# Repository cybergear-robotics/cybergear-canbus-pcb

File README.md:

# CyberGear CAN-Bus PCB

This is a small extension board located on the CyberBot. It distributes the
CAN-bus to all 6 cybergears and provides a debug port. Each cybergear CAN-bus sink can
be switched between CAN-bus or debug port. The can-bus is designed as star
topology, which works in small setups. 

## DIP switches

The switches are missing in the production files and you need to solder these on your
own. The required switches are MSS22D18 Mini DIP Slide Switch 2x03.

## Debug Port

The debug port is connected to a special CAN to USB adapter. There is no product
number. I only could find one offer on Aliexpress for around 12 euros:

```
USB-TTL/RS232/RS485/CAN Serial Communication Module CH340 CP2102 Data Conversion
Transparent Transmission Standard Protocol
```

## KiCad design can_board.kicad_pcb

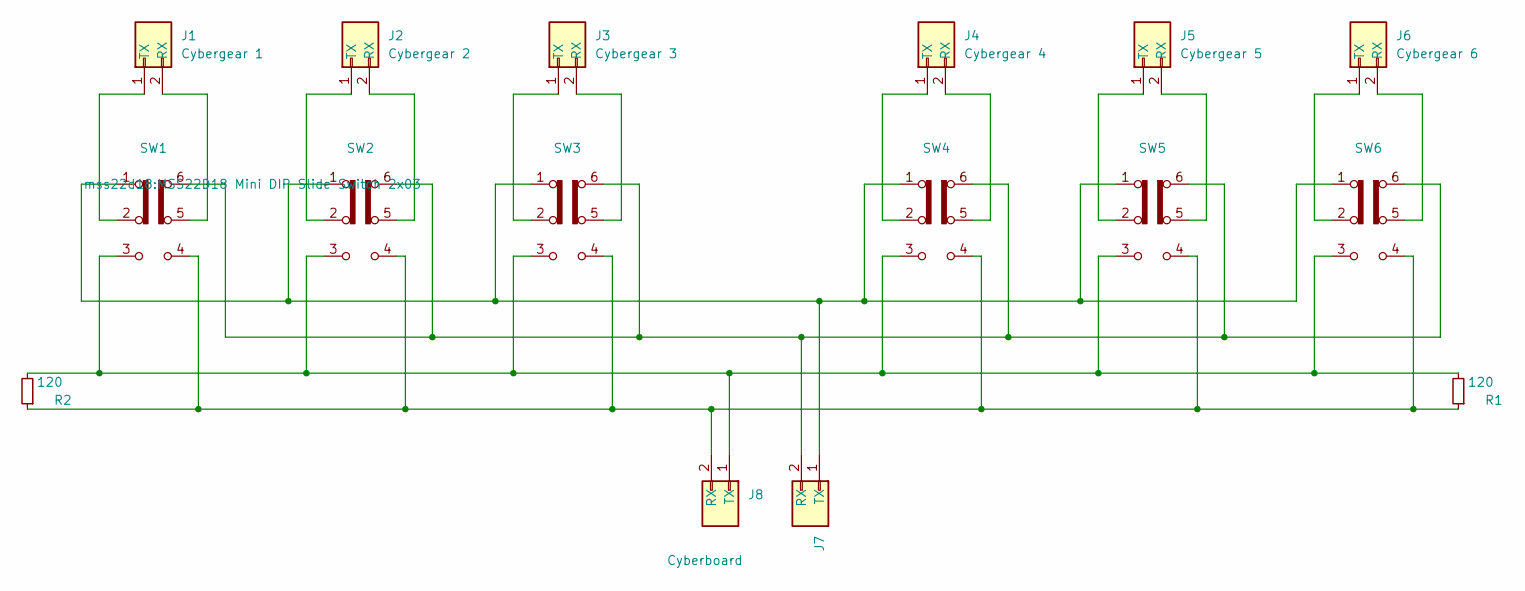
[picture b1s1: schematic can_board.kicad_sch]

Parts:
J1: Cybergear 1; JST_XH_S2B-XH-A-1_1x02_P2.50mm_Horizontal
J2: Cybergear 2; JST_XH_S2B-XH-A-1_1x02_P2.50mm_Horizontal
J3: Cybergear 3; JST_XH_S2B-XH-A-1_1x02_P2.50mm_Horizontal
J4: Cybergear 4; JST_XH_S2B-XH-A-1_1x02_P2.50mm_Horizontal
J5: Cybergear 5; JST_XH_S2B-XH-A-1_1x02_P2.50mm_Horizontal
J6: Cybergear 6; JST_XH_S2B-XH-A-1_1x02_P2.50mm_Horizontal
J7: Debug; JST_XH_S2B-XH-A-1_1x02_P2.50mm_Horizontal
J8: Cyberboard; JST_XH_S2B-XH-A-1_1x02_P2.50mm_Horizontal
R1, R2: 120; R_0805_2012Metric; LCSC C17437
SW1, SW2, SW3, SW4, SW5, SW6: SW_Slide_DPDT; MSS22D18 Mini DIP Slide Switch 2x03

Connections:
unnamed: J1.2 (RX), SW1.5 (B)
unnamed: J1.1 (TX), SW1.2 (B)
unnamed: J2.2 (RX), SW2.5 (B)
unnamed: J2.1 (TX), SW2.2 (B)
unnamed: J3.2 (RX), SW3.5 (B)
unnamed: J3.1 (TX), SW3.2 (B)
unnamed: J4.2 (RX), SW4.5 (B)
unnamed: J4.1 (TX), SW4.2 (B)
unnamed: J5.2 (RX), SW5.5 (B)
unnamed: J5.1 (TX), SW5.2 (B)
unnamed: J6.2 (RX), SW6.5 (B)
unnamed: J6.1 (TX), SW6.2 (B)
unnamed: J7.2 (RX), SW1.6 (C), SW2.6 (C), SW3.6 (C), SW4.6 (C), SW5.6 (C), SW6.6 (C)
unnamed: J7.1 (TX), SW1.1 (A), SW2.1 (A), SW3.1 (A), SW4.1 (A), SW5.1 (A), SW6.1 (A)
unnamed: J8.2 (RX), R1.1, R2.1, SW1.4 (A), SW2.4 (A), SW3.4 (A), SW4.4 (A), SW5.4 (A), SW6.4 (A)
unnamed: J8.1 (TX), R1.2, R2.2, SW1.3 (C), SW2.3 (C), SW3.3 (C), SW4.3 (C), SW5.3 (C), SW6.3 (C)

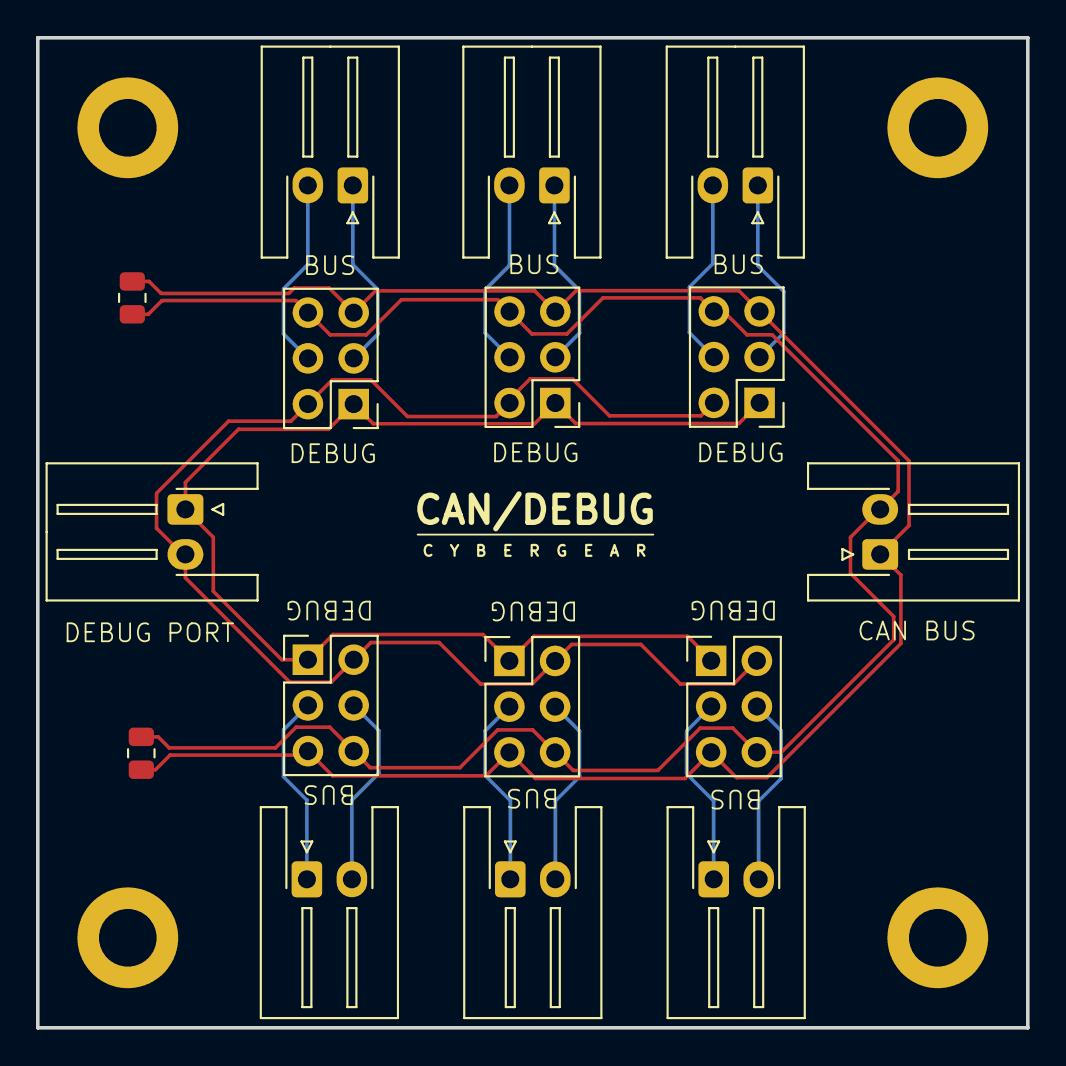
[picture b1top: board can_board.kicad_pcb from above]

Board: 2 copper layers, 55.0 x 55.0 mm, 20 parts (0 on the bottom side), 16 nets.

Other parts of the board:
H1, H2, H3, H4: MountingHole_Pad; MountingHole_3.2mm_M3_DIN965_Pad

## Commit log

2025-02-20 inital design for can-board
2025-03-31 add license and README

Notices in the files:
README.md:
License: MIT
